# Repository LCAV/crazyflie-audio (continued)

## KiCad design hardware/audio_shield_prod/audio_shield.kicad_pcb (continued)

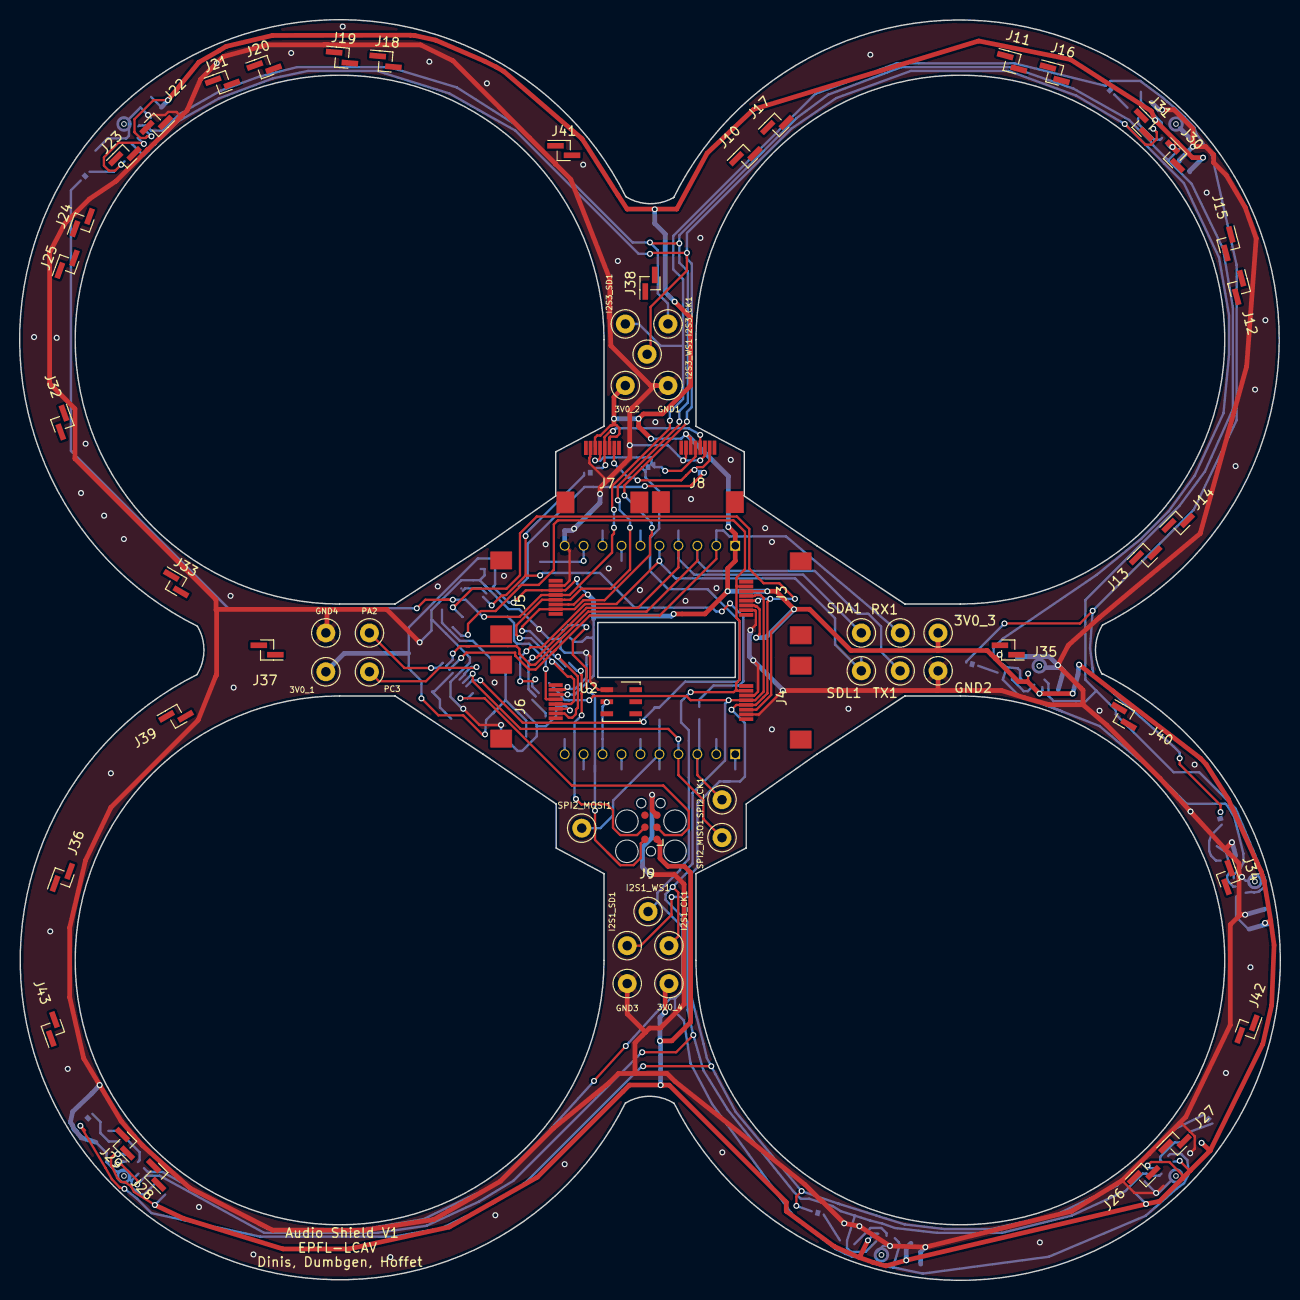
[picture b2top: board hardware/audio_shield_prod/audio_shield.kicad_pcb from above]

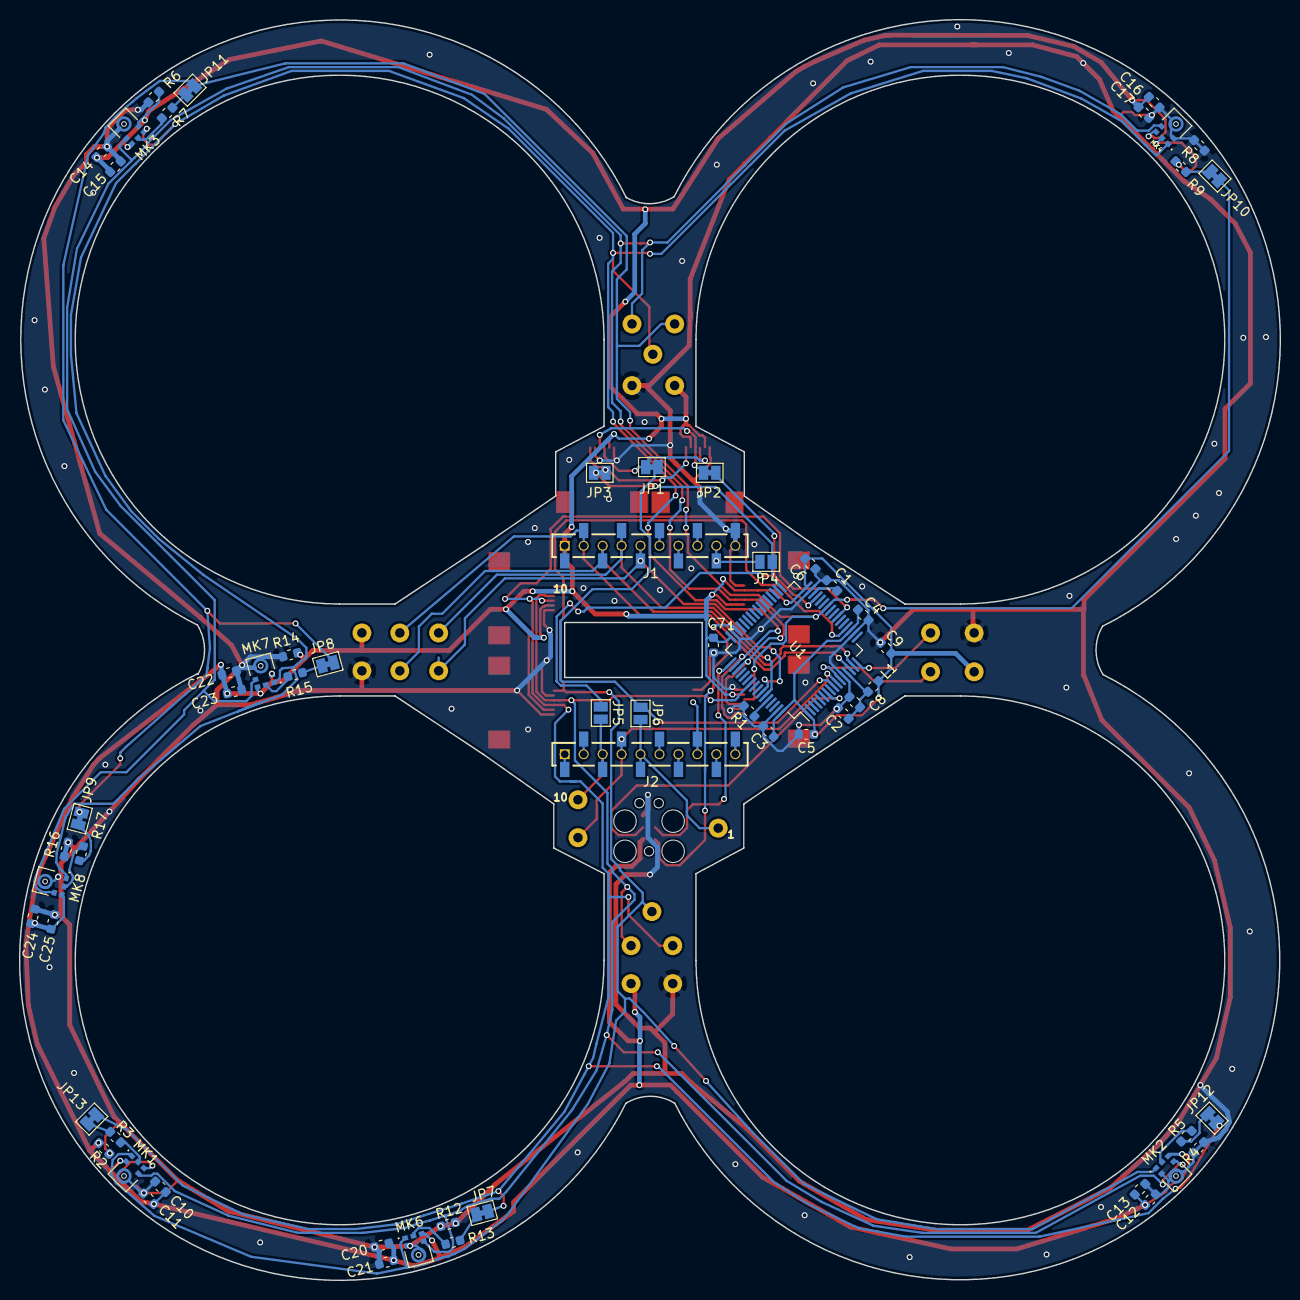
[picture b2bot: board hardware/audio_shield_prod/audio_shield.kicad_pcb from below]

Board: 2 copper layers, 133.0 x 133.0 mm, 127 parts (62 on the bottom side), 45 nets.

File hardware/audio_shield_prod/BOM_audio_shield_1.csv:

"Source:","/Users/hoffet/Dropbox/Documents Adrien/Jobs Data/LCAV/audio_shield 4/audio_shield.sch"
"Date:","2020 July 21, Tuesday 14:52:48"
"Tool:","Eeschema (5.1.6-0-10_14)"
"Generator:","/private/var/folders/_0/5tv0ncr12mg82wg0rc7s58xw0000gp/T/AppTranslocation/C6C6CB14-3D46-4291-8C46-232F0E03D8E1/d/kicad.app/Contents/SharedSupport/plugins/bom_csv_grouped_by_value_with_fp.py"
"Component Count:","126"
"Ref","Qnty","Value","Cmp name","Footprint","Description","Vendor"
"3V0_1, 3V0_2, 3V0_3, 3V0_4, GND1, GND2, GND3, GND4, I2S1_CK1, I2S1_SD1, I2S1_WS1, I2S3_CK1, I2S3_SD1, I2S3_WS1, PA2, PC3, RX1, SDA1, SDL1, SPI2_CK1, SPI2_MISO1, SPI2_MOSI1, TX1, ","23","TestPoint","TestPoint","audio_shield:TestPoint_Loop_D2.50mm_Drill1.0mm_LowProfile","test point",""
"C1, C9, ","2","4.7u","C","Capacitor_SMD:C_0603_1608Metric","Unpolarized capacitor",""
"C2, C3, C4, C5, C6, C7, C11, C13, C15, C17, C21, C23, C25, ","13","100n","C","Capacitor_SMD:C_0603_1608Metric","Unpolarized capacitor",""
"C8, ","1","1u","C","Capacitor_SMD:C_0603_1608Metric","Unpolarized capacitor",""
"C10, C12, C14, C16, C20, C22, C24, ","7","220p","C","Capacitor_SMD:C_0603_1608Metric","Unpolarized capacitor",""
"J1, ","1","CONN_10_LEFT","Conn_01x10","audio_shield:BF090-10-X-B2","Generic connector, single row, 01x10, script generated (kicad-library-utils/schlib/autogen/connector/)",""
"J2, ","1","CONN_10_RIGHT","Conn_01x10","audio_shield:BF090-10-X-B2","Generic connector, single row, 01x10, script generated (kicad-library-utils/schlib/autogen/connector/)",""
"J3, J4, J5, J6, J7, J8, ","6","mic_connector","mic_connector","audio_shield:6288_series_8_pos","",""
"J9, ","1","SWD_TC2030","SWD_TC2030","Connector:Tag-Connect_TC2030-IDC-FP_2x03_P1.27mm_Vertical","",""
"J10, J11, J12, J13, J14, J15, J16, J17, J18, J19, J20, J21, J22, J23, J24, J25, J26, J27, J28, J29, J30, J31, J32, J33, J34, J35, J36, J37, J38, J39, J40, J41, J42, J43, ","34","Conn_01x02_Male","Conn_01x02_Male","Connector_PinHeader_1.00mm:PinHeader_1x02_P1.00mm_Vertical_SMD_Pin1Left","Generic connector, single row, 01x02, script generated (kicad-library-utils/schlib/autogen/connector/)",""
"JP1, JP2, JP3, JP7, JP8, JP9, JP10, JP11, JP12, JP13, ","10","Jumper","Jumper","Jumper:SolderJumper-2_P1.3mm_Bridged_Pad1.0x1.5mm","Jumper, normally closed",""
"JP4, JP5, JP6, ","3","Jumper","Jumper","Jumper:SolderJumper-2_P1.3mm_Open_Pad1.0x1.5mm","Jumper, normally closed",""
"L1, ","1","2.2uH/15mA","L","Inductor_SMD:L_0603_1608Metric","Inductor",""
"MK1, MK2, MK3, MK4, MK6, MK7, MK8, ","7","SPH0645LM4H-B","SPH0645LM4H-B","audio_shield:MIC_SPH0645LM4H-B","",""
"R1, R2, R4, R6, R8, R12, R14, R16, ","8","10k","R","Resistor_SMD:R_0603_1608Metric","Resistor",""
"R3, R5, R7, R9, R13, R15, R17, ","7","68","R","Resistor_SMD:R_0603_1608Metric","Resistor",""
"U1, ","1","STM32F446RETx","STM32F446RETx","Package_QFP:LQFP-64_10x10mm_P0.5mm","ARM Cortex-M4 MCU, 512KB flash, 128KB RAM, 180MHz, 1.8-3.6V, 50 GPIO, LQFP-64",""

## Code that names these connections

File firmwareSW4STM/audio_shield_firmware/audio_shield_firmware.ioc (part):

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Mcu.Name=STM32F446R(C-E)Tx
Mcu.Package=LQFP64
Mcu.UserName=STM32F446RETx
PA13.GPIOParameters=GPIO_Label
PA13.GPIO_Label=TMS
PA13.Mode=Serial_Wire
PA13.Signal=SYS_JTMS-SWDIO
PA14.GPIOParameters=GPIO_Label
PA14.GPIO_Label=TCK
PA14.Mode=Serial_Wire
PA14.Signal=SYS_JTCK-SWCLK
PA15.Mode=Half_Duplex_Master
PA15.Signal=I2S3_WS
PA2.Signal=GPIO_Output
PA4.Mode=Half_Duplex_Master
PA4.Signal=I2S1_WS
PA7.Mode=Half_Duplex_Master
PA7.Signal=I2S1_SD
PB0.Mode=Half_Duplex_Master
PB0.Signal=I2S3_SD
PB10.GPIOParameters=GPIO_PuPd
PB10.GPIO_PuPd=GPIO_NOPULL
PB10.Mode=Full_Duplex_Slave
PB10.Signal=SPI2_SCK
PB12.Mode=NSS_Signal_Hard_Input
PB12.Signal=SPI2_NSS
PB3.Mode=Half_Duplex_Master
PB3.Signal=I2S1_CK
PC1.GPIOParameters=GPIO_PuPd
PC1.GPIO_PuPd=GPIO_NOPULL
PC1.Mode=Full_Duplex_Slave
PC1.Signal=SPI2_MOSI
PC10.Mode=Half_Duplex_Master
PC10.Signal=I2S3_CK
PC14-OSC32_IN.Mode=LSE-External-Oscillator
PC14-OSC32_IN.Signal=RCC_OSC32_IN
PC15-OSC32_OUT.Mode=LSE-External-Oscillator
PC15-OSC32_OUT.Signal=RCC_OSC32_OUT
PC2.GPIOParameters=GPIO_PuPd
PC2.GPIO_PuPd=GPIO_NOPULL
PC2.Mode=Full_Duplex_Slave
PC2.Signal=SPI2_MISO
PC3.Signal=GPIO_Output
PH0-OSC_IN.Mode=HSE-External-Oscillator
PH0-OSC_IN.Signal=RCC_OSC_IN
PH1-OSC_OUT.Mode=HSE-External-Oscillator
PH1-OSC_OUT.Signal=RCC_OSC_OUT
RCC.HSE_VALUE=8000000
RCC.SYSCLKFreq_VALUE=84000000
RCC.SYSCLKSource=RCC_SYSCLKSOURCE_PLLCLK
board=NUCLEO-F446RE
boardIOC=true

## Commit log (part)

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2020-07-28 Add .gitignore to ignore workspace specific folders
2020-07-28 Renamed firmware.
2020-07-28 Cleanup project
2020-07-28 Edit gitinore to add libraries
2020-07-28 Add missing libraries.
2020-07-28 Edit gitinore to remove .bin
2020-07-28 Renamed memory dump folder.
2020-07-28 Created toy example for complex matrix multiplication.
2020-07-28 Remove objects.list
2020-07-28 Fix matrix multiplication.
2020-07-29 Fix matrix inverse
2020-07-29 Optimise code
2020-07-29 Update PCB info after footprint missmatch
2020-07-29 Renamed some data files.
2020-07-29 Repaired flight script, added gitignore.
2020-07-29 Cleaned flight script.
2020-07-29 edit .ioc and corresponding c files to adapt to the pcb pinout
2020-07-31 fix last commit
2020-08-07 added documentation for PID tuning
2020-08-11 Added original files.
2020-08-11 Cleaned and fixed files.
2020-08-14 fix pinout issue on stm32
2020-08-18 Create corr_matrix_packet.py
    added python script to recover correlation matrix through CRTP
2020-08-18 added better comments
2020-08-18 Implement different byte conversion (to be tested)
2020-08-18 clean code and comment matrix calculation
2020-08-18 added I2C configuration
2020-08-18 Fix previous commit
2020-08-18 reset project files
2020-08-18 change buffer size and fix gitignore
2020-08-18 remove ignored files
2020-08-18 fix R and I indexes
2020-08-18 Fix print
2020-08-19 added thrust while sending packets
2020-08-19 flipped and changed audio deck crazyflie pins + added identification EEPROM
2020-08-19 annotation added
2020-08-19 Add tapering window creation script and implementation in audiodeck firmware
2020-08-19 Remove .pyc files
2020-08-19 Edit component attribute for eurocircuit manufacturing
2020-08-20 Revert "not shure what I do"
    This reverts commit 37857eb5b53a0fb98869ec0b4d1d0d15ce312f00, reversing
    changes made to 0b65fa19d0ccbf03451c7e7100d005444b2b7b70.
2020-08-20 Revert "Revert "not shure what I do""
    This reverts commit c38e20f0cd3f4d4c62a5fd8c8ef8a2b8178c72d3.
2020-08-20 reset PCB file to 83b76c623
2020-08-20 Remove duplicate line
2020-08-24 Renamed script
2020-08-24 Start refactoring
2020-08-24 add bin selection script
2020-08-25 Rename CRTP reader
2020-08-25 Finish motion reading
2020-08-25 fix uniform bin selection, still miss some bin but they are correctly placed now, tbc
2020-08-25 Add timestamp and z, refactoring
2020-08-25 Update firmware
2020-08-25 added thrust receive function to the audio deck firmware
2020-08-25 fixed bug
2020-08-25 Fix timestamps
2020-08-25 Fix logging
2020-08-25 Reduce logging period
2020-08-26 Add doc for spectrum warping
2020-08-27 fixed bin selection python
2020-08-27 fix semaphore for audio samples
2020-08-27 final bin selection methon in C
2020-08-27 added function to receive I2C parameters
2020-08-27 Remove motor param function prototype
2020-08-27 change bin selection script
2020-08-27 Add frequency bin reading (needs testing)
2020-08-27 Fix small typos
2020-08-27 added sending of fbins
2020-08-27 modify bin selection
2020-08-27 minor fix
2020-08-27 fixed ? crtp reader
2020-08-27 Refactor file parser
2020-08-28 small fix
2020-08-31 Refactor CRTP reading
2020-08-31 Improve printing
2020-08-31 Receive frequency bins through CRTP (#2)
    * Add frequency bin reading (needs testing)
    * Fix small typos
    * Fix channel reading
    * fixed ? crtp reader
    * small fix
    * Refactor CRTP reading
2020-09-01 debug file_parser
2020-09-01 Improve verbose setting
2020-09-01 fix bin selection and embded implementation
2020-09-01 Correct frequency selection sending and general cleaning
2020-09-01 test to have bidirectionnal communication
2020-09-01 last tentative of the day, to be tested
2020-09-02 Update experiment evaluation
2020-09-02 Fix Fs handling
2020-09-02 Create cleaner bin selection
2020-09-02 Rename parameters to match ROS
2020-09-03 Update docs and submodule
2020-09-03 Cleanup
2020-09-03 Implement basic i2s communication
2020-09-03 Update freq range
2020-09-03 Update submodule
2020-09-03 Create firmware from scratch
2020-09-03 Add debug launch file
2020-09-03 Copy source code
2020-09-04 last state of the debuging from 03.09.20
2020-09-04 Added hardfault debugging code, tried different DMA priorities
2020-09-04 Verify bin selection with 1024 buffer
2020-09-04 Renamed and added delta_freq
2020-09-04 Improve fbin_selection
2020-09-07 Add fast MVDR implementation
2020-09-07 Add bin selection changes from testSPI branch
2020-09-10 Working (slow) spi version
2020-09-10 Add timers and fault checks
2020-09-10 Remove unnecessary files.
2020-09-10 Remove unused variable
2020-09-10 Remove unused files
2020-09-10 Ubuntu cubemx (#3)
2020-09-11 Remove tapering window and change simulated data
2020-09-11 Change data communication flow, first atempt
2020-09-14 Debugging version of SPI
2020-09-14 Add oscillo file
2020-09-14 Add fixed checksum on audio deck
2020-09-15 Robust example with N=5
2020-09-15 Reuse real data
2020-09-16 Remove unused and fix indentation
2020-09-16 Formatting
2020-09-16 Add microphone layout.
2020-09-16 Add synch check option
2020-09-17 Add motor do doc, and rx_synch reset
2020-09-18 Fix documentation
2020-09-18 Added reaper files
2020-09-30 Correct frequency selection and change averaging method
2020-09-30 Implement motor thrust averaging
2020-09-30 Add IIR averaging
2020-10-13 Clean up code
2020-10-13 Add prop_freq declaration
2020-10-13 Create signals increasing in volume
2020-10-14 Add zero-signal
2020-10-14 Add global variables
2020-10-20 add fabrication files for eurocircuit
2020-10-20 add timestamps in deck messages
2020-10-20 correct typo
2020-10-20 Fix motor powrt issue
2020-10-20 fix timestamp before fft
2020-10-20 fix bug
2020-10-20 Implement python reading
2020-10-22 Change NSS workflow
2020-10-22 Remove submodule
2020-10-22 Add flight control scripts
2020-10-23 Created working setup
2020-10-23 Disentangle ArrayCRTP
2020-10-23 Added C project settings files back to git
2020-10-23 Update launch file
2020-10-23 Add debugging state
2020-10-23 Reset to experiment version
2020-10-23 Finish refactoring CRTP reader
2020-10-26 Add hardware NSS
2020-10-26 Remove core directory
2020-10-26 Try to stabilize communicaition.. still not fine
2020-10-27 Supposedly still working (to be tested)
2020-10-28 Add checksum
2020-10-28 Use Receive only
2020-10-28 Switch to DMA
2020-10-28 Working at 300
2020-10-28 Working at 1100
2020-10-29 Remove unused code
2020-10-29 Use memcpy wherever possible
2020-10-29 Fix timestamp publishing
2020-10-29 Fix float conversion
2020-10-29 Reformatting and change of orders
2020-10-29 Add update rate
2020-11-02 Fix tapering window and remove unnecessary cubemx params
2020-11-02 Add tukey length check
2020-11-03 Add sweep and fix loudness calculation
2020-11-04 Fix averaging
2020-11-05 Change mic order to match naming on pcb
2020-11-05 Add EEPROM to README
2020-11-05 Add buzzer in flight test
2020-11-11 Add inverse option
2020-11-11 Send all bins when fewer than requested available
2020-11-11 Convert Warning to print
2020-11-12 Edit soundcard choice
2020-11-12 Added motion commands
2020-11-16 Change speed of sound to match pyroomacoustics
2020-11-16 Add phase offset
2020-11-17 Small changes in flight control
2020-11-17 add how to OW
2020-11-17 edit gitignore to hide info-cache file of kicad
2020-11-17 change gitignore
2020-11-18 Change USB soundcard name
2020-11-19 Add buzzer commands
2020-11-19 minor updates
2020-11-19 add rotating table firmware
2020-11-19 Add chirp generator
2020-11-19 Finalize chirp generator
2020-11-20 Adjust timings
2020-11-23 Clean serial commands
2020-11-23 Add battery check and verbose flag
2020-11-24 Remove language settings
2020-11-25 Adjust bin_selection
2020-11-26 add stepper firmware and change motor and parameters
2020-11-26 Fix serial motors
2020-11-26 Fix type issue
2020-11-27 Add battery static variable
2020-11-28 Status for 2020_11_27_wall_short experiments
2020-11-30 Improve channel reading
2020-12-01 Add motors reading
2020-12-02 Fix move command
2020-12-02 Add types to loggers
2020-12-02 Create new chirp signal
2020-12-03 Create hardcoded frequency sweep
2020-12-04 Add 50cm commands, lower battery-ok-voltage
2020-12-04 change microstepping and add 50cm distance + comments
2020-12-07 Rename SWEEPS
2020-12-07 Fix microstepping
2020-12-07 Fix movement counter
2020-12-07 Change blocking of turn
2020-12-07 Lower battery check
2020-12-09 Adjust battery level
2020-12-11 Add new buzzer
2020-12-17 Fix microphone designations
2020-12-18 Add buzzer frequency index to parameters
2020-12-18 Adjust velocity
2020-12-18 Add new chirps
2020-12-18 Add forward command
2020-12-18 Add new send_audio_enable function
2021-01-04 Minor tweak bin_selection
2021-01-05 Add frequency comparison txt
2021-01-06 Add more values to motion logging
2021-01-06 Create zero-signal function
2021-01-08 Add n_freqs option
2021-01-14 Add frequency study
2021-01-19 Working implementation of IIR With 2 coef
2021-01-21 Fix code error
2021-01-21 Remove tukey window with define
2021-01-26 Clean up chirp generation
2021-02-09 Implement bin selection
2021-02-09 Add snr=3 option
2021-02-10 Add generic move and turn functions
2021-02-10 Fix typos
2021-02-11 Renaming
2021-02-11 Reset bin selection, enhance serial motors
2021-02-19 Make windowing programmatically changeable
2021-02-19 Clean window_value initialization
2021-02-19 Clean initialization
2021-02-23 Add new sweep
2021-02-25 Remove hard bins option
2021-03-08 Calculate correction factors
2021-03-25 Integrate window correction
2021-04-05 Clean windows and bin selection
2021-04-09 new averaging
2021-04-09 add hardware V3
2021-04-09 fix issues with big refactoring
2021-04-19 Improve state machine
2021-04-19 Update drivers
2021-04-21 Rewrote state machine
2021-04-21 Improve pwm tuning script
2021-04-21 Revert more changes
2021-04-22 Adapt to new state machine
2021-04-22 Working version
2021-04-22 Remove averaging
2021-04-22 Add LED welcome and basic mic response
2021-04-22 Fix buzzer timer
2021-04-23 Debugging SPI
2021-04-27 Code cleanup
2021-04-28 Reformatting
2021-04-28 Add pre-commit
2021-04-29 Workin version (on new drone)
2021-04-29 Adjust parameters
2021-04-29 Add wake-up melody
2021-04-30 Optimize sweep
2021-04-30 Add timestamp
2021-04-30 Improve buzzer handling
2021-04-30 Update hardware V3 with correct version
2021-05-03 Add new sweep and update pre-commit
2021-05-04 Add break and modify sweep
2021-06-03 Switch LED on at startup
2021-06-03 Initial modifications not fully tested
2021-06-03 fix stuffs whoohoooo
2021-06-08 Integrate the external buzzer mode hardcoded
2021-06-08 Add Buzzer_idx == 5 for external source
2021-06-17 Add epuck sweep
2021-06-17 Fix buggy sequence
2021-06-17 Add windows of length 1024
2021-06-17 Fix hann window
2021-06-17 Stable version with half buffer and longer delay
2021-06-17 Create windows for N=1024
2021-06-17 Start fixing snr selection
2021-06-17 Fix state machine, working
2021-06-17 interupt mode
2021-06-17 working version with interrupt (pipeline not tested)
2021-06-17 Reactivate spi synchronisation
2021-06-19 Implement SNR selection (not tested yet)
2021-06-19 Implement windowing around current frequency
2021-06-19 Adjust sweeps
2021-06-19 Add mono sweeps
2021-06-19 Create new sweeps
2021-06-22 Implement longer sweep
2021-06-22 Rename filter_snr_enable
2021-07-08 Fast version with sample to process > 1 ( and fix synch)
2021-07-08 Change sweep 2500--4500
2021-07-14 Adjust sweep used
2021-09-23 add rotating table recovery project
2021-09-23 Add command for 5 deg increments
2021-09-28 fix typo for rotation commands
2021-09-30 Add 30 degrees command to serial motors
2021-10-04 Improve naming and fix size
2021-10-05 Adjust buffer sizes
2021-10-05 Fix mic names, regenerate code
2021-10-05 Fix all issues whoowhoo
2021-10-05 fix everything again^^
2021-10-07 Remove monitoring
2021-10-07 Generate new sweep compatible with 48000
2021-10-13 Added todo notes for things to be fixed
2021-10-14 FIX AND TEST DISTANCE/ANGLE
2021-10-14 Fix commands
2021-10-14 Change array length to 24
2021-10-14 Introduce new functions
2021-11-16 Added files from backup
2022-03-02 Remove unused components
2022-03-02 Update firmware link
